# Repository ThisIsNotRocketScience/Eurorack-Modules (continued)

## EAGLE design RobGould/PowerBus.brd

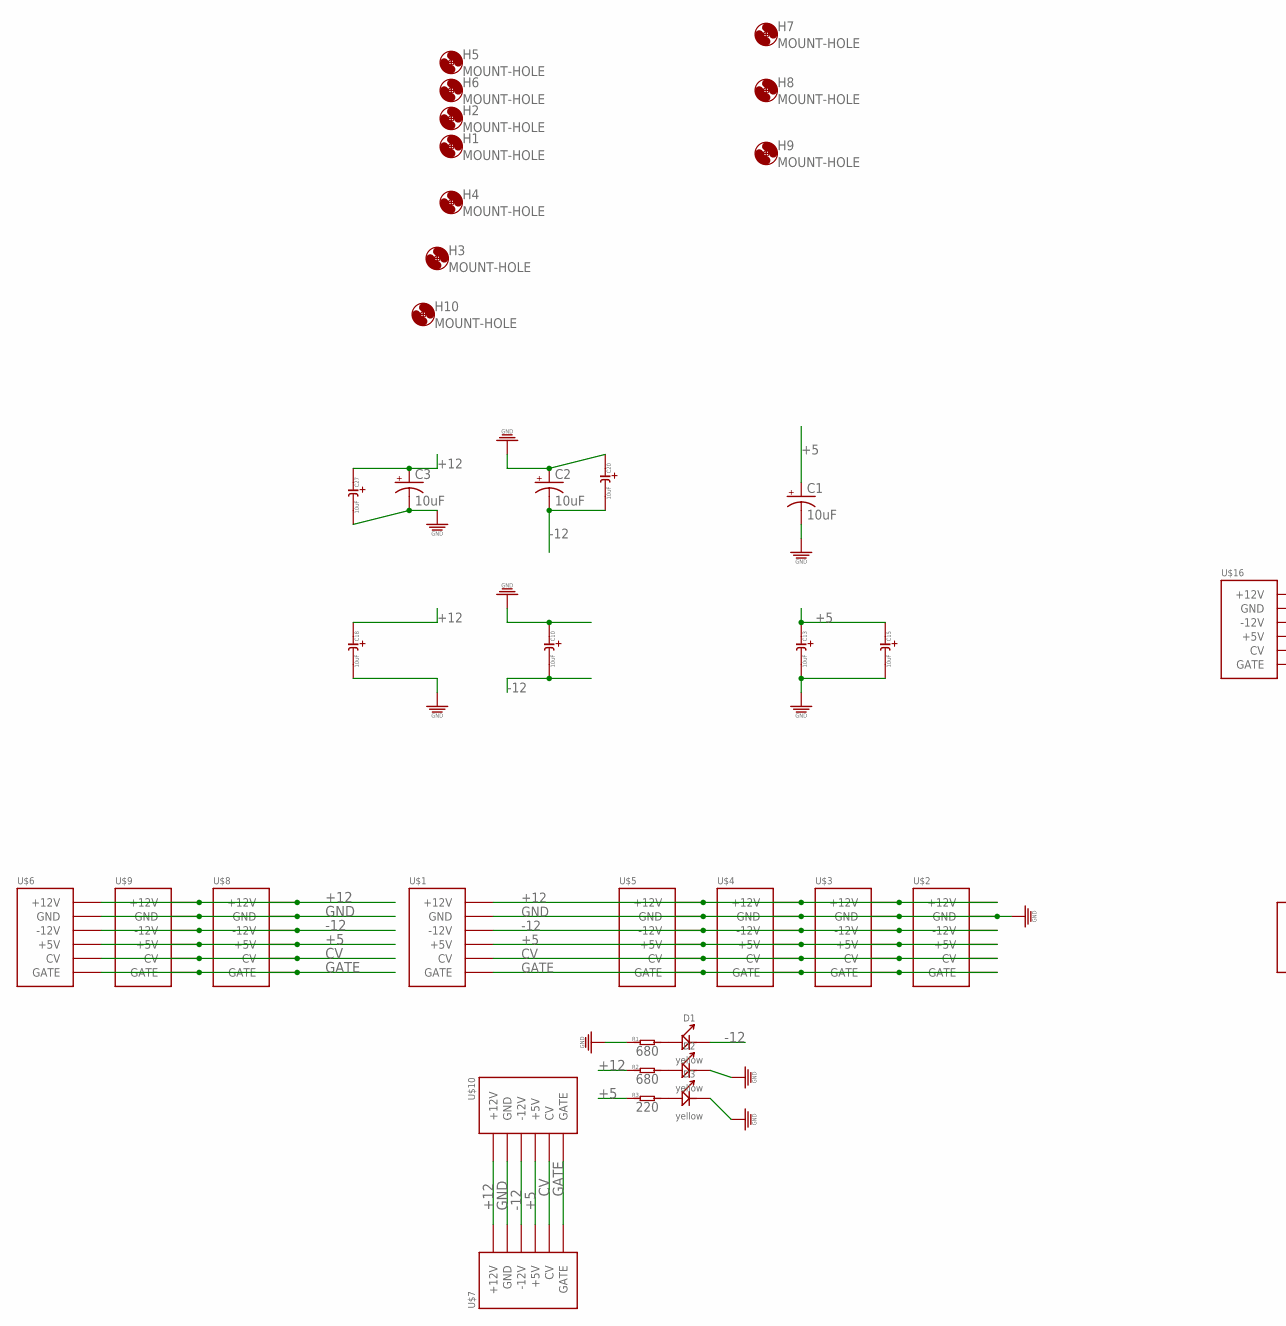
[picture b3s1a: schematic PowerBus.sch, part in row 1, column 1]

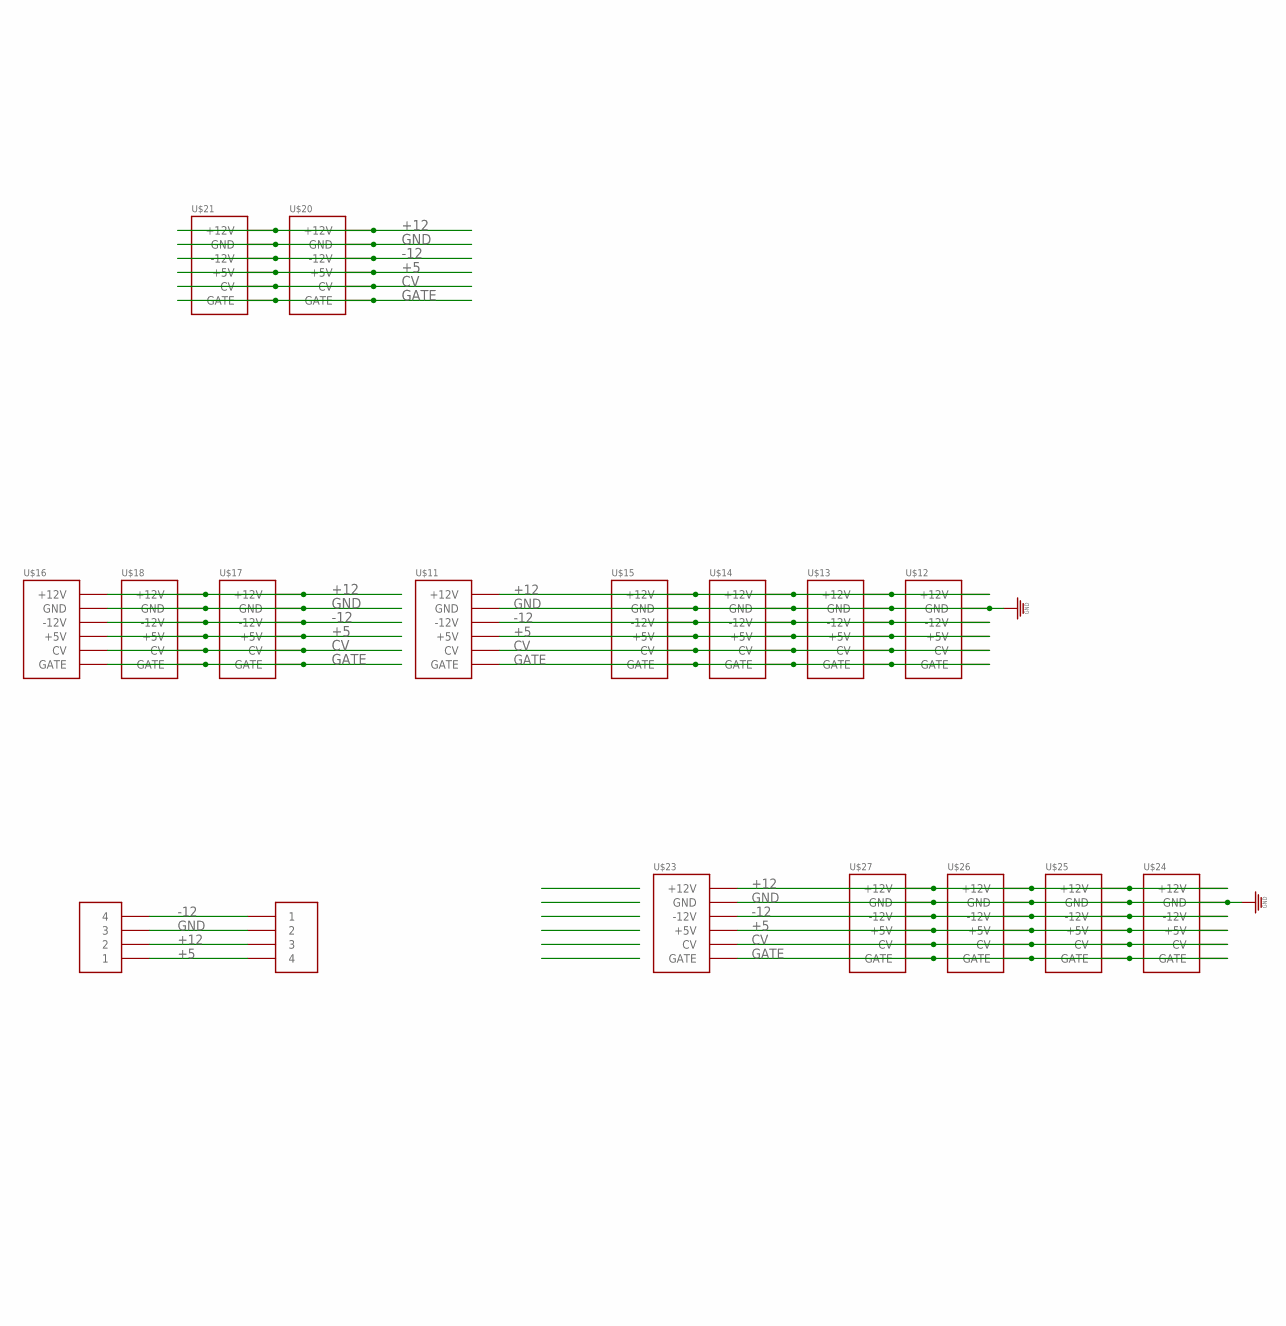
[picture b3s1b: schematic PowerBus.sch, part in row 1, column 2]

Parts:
C1, C2, C3: 10uF; PANASONIC_D
C10, C13, C15, C18, C20, C27: 10uF; CASE-A_3216
D1, D2, D3: yellow; LED0603
H1, H2, H3, H4, H5, H6, H7, H8, H9, H10: MOUNT-HOLE; 3.2-NOMARKINGS-SMALLSAFEZONE
R1, R2: 680; R0603
R3: 220; R0603
U$1, U$2, U$3, U$4, U$5, U$6, U$7, U$8, U$9, U$10, U$11, U$12, U$13, U$14, U$15, U$16, U$17, U$18, U$20, U$21, U$23, U$24, U$25, U$26, U$27: POWER_SHROUDED_NOTEXT; POWER_16_SHROUDED_NOTEXT
U$19, U$22: 4PIN5MM

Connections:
+5: C1.+, C13.+ (1), C15.+ (1), R3.1, U$1.11 (+5V), U$1.12 (+5V), U$2.11 (+5V), U$2.12 (+5V), U$3.11 (+5V), U$3.12 (+5V), U$4.11 (+5V), U$4.12 (+5V), U$5.11 (+5V), U$5.12 (+5V), U$6.11 (+5V), U$6.12 (+5V), U$7.11 (+5V), U$7.12 (+5V), U$8.11 (+5V), U$8.12 (+5V), U$9.11 (+5V), U$9.12 (+5V), U$10.11 (+5V), U$10.12 (+5V), U$11.11 (+5V), U$11.12 (+5V), U$12.11 (+5V), U$12.12 (+5V), U$13.11 (+5V), U$13.12 (+5V), U$14.11 (+5V), U$14.12 (+5V), U$15.11 (+5V), U$15.12 (+5V), U$16.11 (+5V), U$16.12 (+5V), U$17.11 (+5V), U$17.12 (+5V), U$18.11 (+5V), U$18.12 (+5V), U$19.4, U$20.11 (+5V), U$20.12 (+5V), U$21.11 (+5V), U$21.12 (+5V), U$22.1, U$23.11 (+5V), U$23.12 (+5V), U$24.11 (+5V), U$24.12 (+5V), U$25.11 (+5V), U$25.12 (+5V), U$26.11 (+5V), U$26.12 (+5V), U$27.11 (+5V), U$27.12 (+5V)
+12: C3.+, C18.+ (1), C27.+ (1), R2.1, U$1.9 (+12V), U$1.10 (+12V), U$2.9 (+12V), U$2.10 (+12V), U$3.9 (+12V), U$3.10 (+12V), U$4.9 (+12V), U$4.10 (+12V), U$5.9 (+12V), U$5.10 (+12V), U$6.9 (+12V), U$6.10 (+12V), U$7.9 (+12V), U$7.10 (+12V), U$8.9 (+12V), U$8.10 (+12V), U$9.9 (+12V), U$9.10 (+12V), U$10.9 (+12V), U$10.10 (+12V), U$11.9 (+12V), U$11.10 (+12V), U$12.9 (+12V), U$12.10 (+12V), U$13.9 (+12V), U$13.10 (+12V), U$14.9 (+12V), U$14.10 (+12V), U$15.9 (+12V), U$15.10 (+12V), U$16.9 (+12V), U$16.10 (+12V), U$17.9 (+12V), U$17.10 (+12V), U$18.9 (+12V), U$18.10 (+12V), U$19.3, U$20.9 (+12V), U$20.10 (+12V), U$21.9 (+12V), U$21.10 (+12V), U$22.2, U$23.9 (+12V), U$23.10 (+12V), U$24.9 (+12V), U$24.10 (+12V), U$25.9 (+12V), U$25.10 (+12V), U$26.9 (+12V), U$26.10 (+12V), U$27.9 (+12V), U$27.10 (+12V)
-12: C2.-, C10.- (2), C20.- (2), D1.-, U$1.1 (-12V), U$1.2 (-12V), U$2.1 (-12V), U$2.2 (-12V), U$3.1 (-12V), U$3.2 (-12V), U$4.1 (-12V), U$4.2 (-12V), U$5.1 (-12V), U$5.2 (-12V), U$6.1 (-12V), U$6.2 (-12V), U$7.1 (-12V), U$7.2 (-12V), U$8.1 (-12V), U$8.2 (-12V), U$9.1 (-12V), U$9.2 (-12V), U$10.1 (-12V), U$10.2 (-12V), U$11.1 (-12V), U$11.2 (-12V), U$12.1 (-12V), U$12.2 (-12V), U$13.1 (-12V), U$13.2 (-12V), U$14.1 (-12V), U$14.2 (-12V), U$15.1 (-12V), U$15.2 (-12V), U$16.1 (-12V), U$16.2 (-12V), U$17.1 (-12V), U$17.2 (-12V), U$18.1 (-12V), U$18.2 (-12V), U$19.1, U$20.1 (-12V), U$20.2 (-12V), U$21.1 (-12V), U$21.2 (-12V), U$22.4, U$23.1 (-12V), U$23.2 (-12V), U$24.1 (-12V), U$24.2 (-12V), U$25.1 (-12V), U$25.2 (-12V), U$26.1 (-12V), U$26.2 (-12V), U$27.1 (-12V), U$27.2 (-12V)
CV: U$1.13 (CV), U$1.14 (CV), U$2.13 (CV), U$2.14 (CV), U$3.13 (CV), U$3.14 (CV), U$4.13 (CV), U$4.14 (CV), U$5.13 (CV), U$5.14 (CV), U$6.13 (CV), U$6.14 (CV), U$7.13 (CV), U$7.14 (CV), U$8.13 (CV), U$8.14 (CV), U$9.13 (CV), U$9.14 (CV), U$10.13 (CV), U$10.14 (CV), U$11.13 (CV), U$11.14 (CV), U$12.13 (CV), U$12.14 (CV), U$13.13 (CV), U$13.14 (CV), U$14.13 (CV), U$14.14 (CV), U$15.13 (CV), U$15.14 (CV), U$16.13 (CV), U$16.14 (CV), U$17.13 (CV), U$17.14 (CV), U$18.13 (CV), U$18.14 (CV), U$20.13 (CV), U$20.14 (CV), U$21.13 (CV), U$21.14 (CV), U$23.13 (CV), U$23.14 (CV), U$24.13 (CV), U$24.14 (CV), U$25.13 (CV), U$25.14 (CV), U$26.13 (CV), U$26.14 (CV), U$27.13 (CV), U$27.14 (CV)
GATE: U$1.15 (GATE), U$1.16 (GATE), U$2.15 (GATE), U$2.16 (GATE), U$3.15 (GATE), U$3.16 (GATE), U$4.15 (GATE), U$4.16 (GATE), U$5.15 (GATE), U$5.16 (GATE), U$6.15 (GATE), U$6.16 (GATE), U$7.15 (GATE), U$7.16 (GATE), U$8.15 (GATE), U$8.16 (GATE), U$9.15 (GATE), U$9.16 (GATE), U$10.15 (GATE), U$10.16 (GATE), U$11.15 (GATE), U$11.16 (GATE), U$12.15 (GATE), U$12.16 (GATE), U$13.15 (GATE), U$13.16 (GATE), U$14.15 (GATE), U$14.16 (GATE), U$15.15 (GATE), U$15.16 (GATE), U$16.15 (GATE), U$16.16 (GATE), U$17.15 (GATE), U$17.16 (GATE), U$18.15 (GATE), U$18.16 (GATE), U$20.15 (GATE), U$20.16 (GATE), U$21.15 (GATE), U$21.16 (GATE), U$23.15 (GATE), U$23.16 (GATE), U$24.15 (GATE), U$24.16 (GATE), U$25.15 (GATE), U$25.16 (GATE), U$26.15 (GATE), U$26.16 (GATE), U$27.15 (GATE), U$27.16 (GATE)
GND: C1.-, C2.+, C3.-, C10.+ (1), C13.- (2), C15.- (2), C18.- (2), C20.+ (1), C27.- (2), D2.-, D3.-, R1.1, U$1.3 (GND), U$1.4 (GND), U$1.5 (GND), U$1.6 (GND), U$1.7 (GND), U$1.8 (GND), U$2.3 (GND), U$2.4 (GND), U$2.5 (GND), U$2.6 (GND), U$2.7 (GND), U$2.8 (GND), U$3.3 (GND), U$3.4 (GND), U$3.5 (GND), U$3.6 (GND), U$3.7 (GND), U$3.8 (GND), U$4.3 (GND), U$4.4 (GND), U$4.5 (GND), U$4.6 (GND), U$4.7 (GND), U$4.8 (GND), U$5.3 (GND), U$5.4 (GND), U$5.5 (GND), U$5.6 (GND), U$5.7 (GND), U$5.8 (GND), U$6.3 (GND), U$6.4 (GND), U$6.5 (GND), U$6.6 (GND), U$6.7 (GND), U$6.8 (GND), U$7.3 (GND), U$7.4 (GND), U$7.5 (GND), U$7.6 (GND), U$7.7 (GND), U$7.8 (GND), U$8.3 (GND), U$8.4 (GND), U$8.5 (GND), U$8.6 (GND), U$8.7 (GND), U$8.8 (GND), U$9.3 (GND), U$9.4 (GND), U$9.5 (GND), U$9.6 (GND), U$9.7 (GND), U$9.8 (GND), U$10.3 (GND), U$10.4 (GND), U$10.5 (GND), U$10.6 (GND), U$10.7 (GND), U$10.8 (GND), U$11.3 (GND), U$11.4 (GND), U$11.5 (GND), U$11.6 (GND), U$11.7 (GND), U$11.8 (GND), U$12.3 (GND), U$12.4 (GND), U$12.5 (GND), U$12.6 (GND), U$12.7 (GND), U$12.8 (GND), U$13.3 (GND), U$13.4 (GND), U$13.5 (GND), U$13.6 (GND), U$13.7 (GND), U$13.8 (GND), U$14.3 (GND), U$14.4 (GND), U$14.5 (GND), U$14.6 (GND), U$14.7 (GND), U$14.8 (GND), U$15.3 (GND), U$15.4 (GND), U$15.5 (GND), U$15.6 (GND), U$15.7 (GND), U$15.8 (GND), U$16.3 (GND), U$16.4 (GND), U$16.5 (GND), U$16.6 (GND), U$16.7 (GND), U$16.8 (GND), U$17.3 (GND), U$17.4 (GND), U$17.5 (GND), U$17.6 (GND), U$17.7 (GND), U$17.8 (GND), U$18.3 (GND), U$18.4 (GND), U$18.5 (GND), U$18.6 (GND), U$18.7 (GND), U$18.8 (GND), U$19.2, U$20.3 (GND), U$20.4 (GND), U$20.5 (GND), U$20.6 (GND), U$20.7 (GND), U$20.8 (GND), U$21.3 (GND), U$21.4 (GND), U$21.5 (GND), U$21.6 (GND), U$21.7 (GND), U$21.8 (GND), U$22.3, U$23.3 (GND), U$23.4 (GND), U$23.5 (GND), U$23.6 (GND), U$23.7 (GND), U$23.8 (GND), U$24.3 (GND), U$24.4 (GND), U$24.5 (GND), U$24.6 (GND), U$24.7 (GND), U$24.8 (GND), U$25.3 (GND), U$25.4 (GND), U$25.5 (GND), U$25.6 (GND), U$25.7 (GND), U$25.8 (GND), U$26.3 (GND), U$26.4 (GND), U$26.5 (GND), U$26.6 (GND), U$26.7 (GND), U$26.8 (GND), U$27.3 (GND), U$27.4 (GND), U$27.5 (GND), U$27.6 (GND), U$27.7 (GND), U$27.8 (GND)
unnamed: D1.+, R1.2
unnamed: D2.+, R2.2
unnamed: D3.+, R3.2

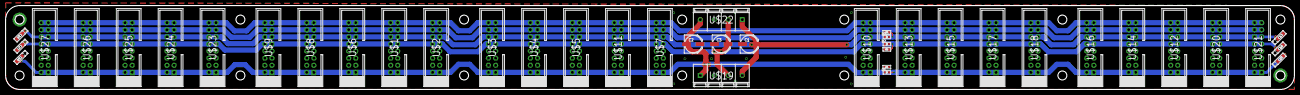
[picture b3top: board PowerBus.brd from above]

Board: 2 copper layers, 461.0 x 30.0 mm, 54 parts (0 on the bottom side), 9 nets.

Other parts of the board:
H11, H12: MOUNT-HOLE; 3.2-NOMARKINGS-SMALLSAFEZONE

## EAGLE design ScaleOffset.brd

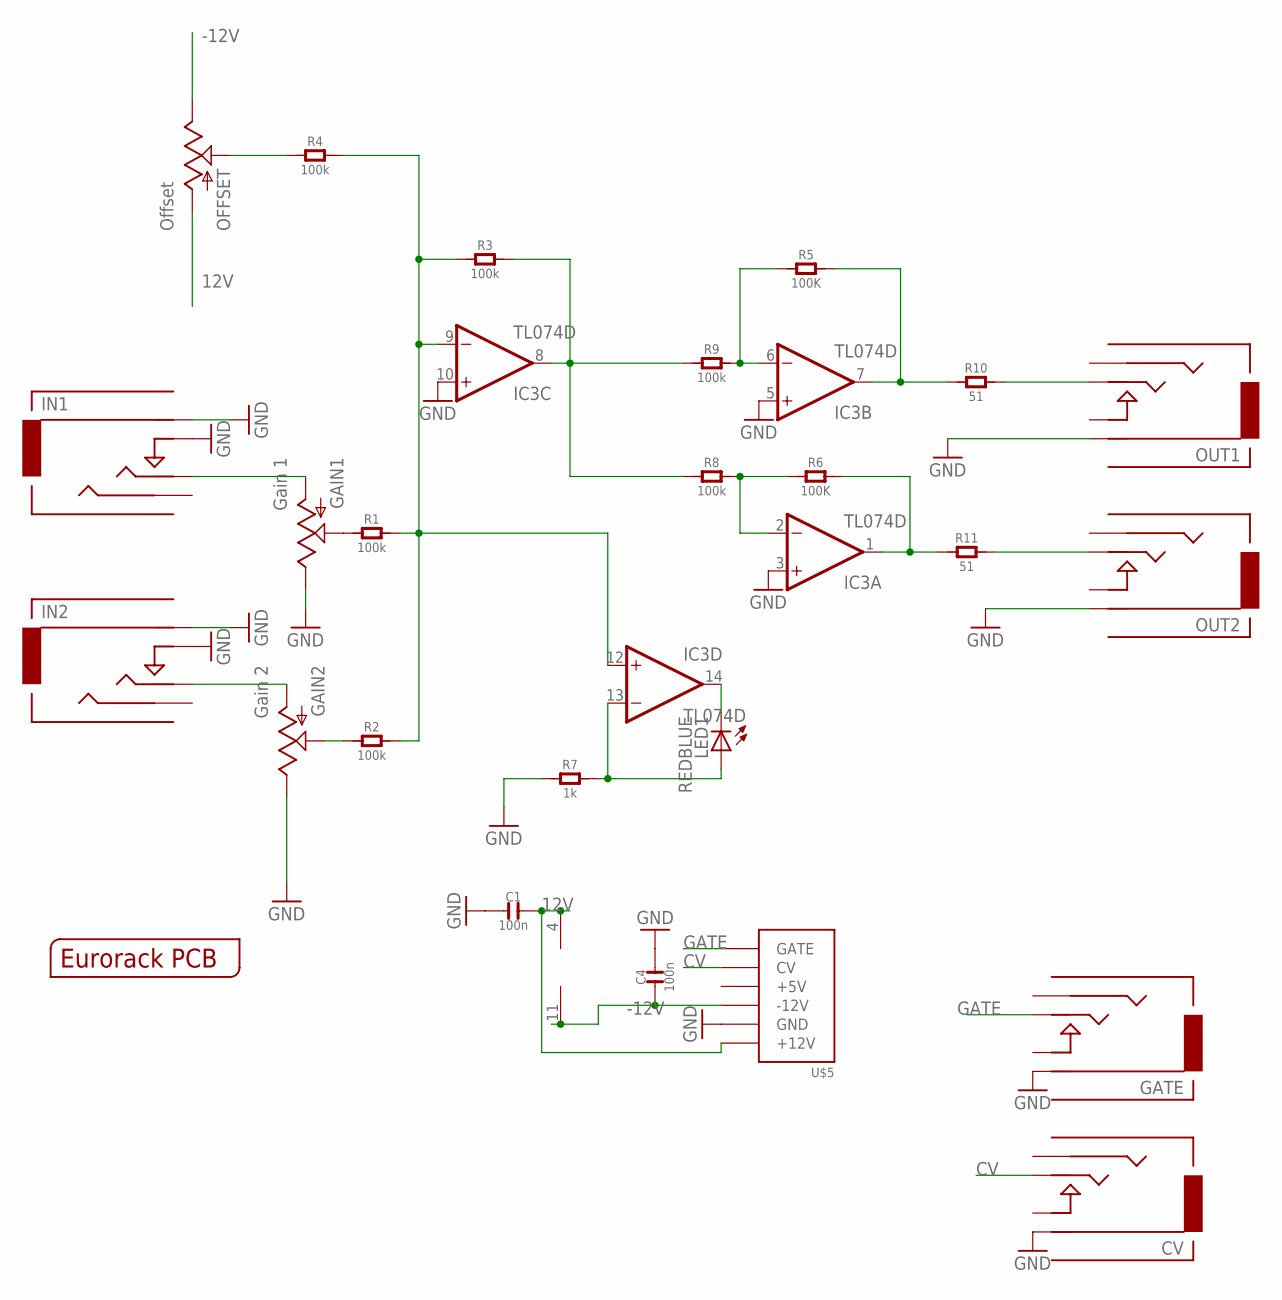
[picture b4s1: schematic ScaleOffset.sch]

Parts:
C1, C4: 100n; C0603
CV: CV; 3.5MM-JACK-SWITCH-13MM-OUTPUT
GAIN1: Gain 1; OG-POTS_ALPS_POT_VERTICAL
GAIN2: Gain 2; OG-POTS_ALPS_POT_VERTICAL
GATE: GATE; 3.5MM-JACK-SWITCH-13MM-OUTPUT
IC3: TL074D; SO14
IN1: Input 1; 3.5MM-JACK-SWITCH-13MM-INPUT
IN2: Input 2; 3.5MM-JACK-SWITCH-13MM-INPUT
LED1: REDBLUE; LED3MM
OFFSET: Offset; OG-POTS_ALPS_POT_VERTICAL
OUT1: 2; 3.5MM-JACK-SWITCH-13MM-OUTPUT
OUT2: 1; 3.5MM-JACK-SWITCH-13MM-OUTPUT
R1, R2, R3, R4, R8, R9: 100k; R0603
R5, R6: 100K; R0603
R7: 1k; R0603
R10, R11: 51; R0603
U$5: POWER; POWER_16
U$12: EURORACK_PCB6HP; EURORACK6HPPCB

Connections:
12V: C1.2, IC3.4 (V+), OFFSET.P$3 (A), U$5.9 (+12V), U$5.10 (+12V)
-12V: C4.1, IC3.11 (V-), OFFSET.P$1 (E), U$5.1 (-12V), U$5.2 (-12V)
CV: CV.TIP@1 (TIP), CV.TIP@2 (TIP), U$5.13 (CV), U$5.14 (CV)
FBOUT1: IC3.7 (OUT), R5.2, R10.1
FBOUT2: IC3.1 (OUT), R6.2, R11.1
GATE: GATE.TIP@1 (TIP), GATE.TIP@2 (TIP), U$5.15 (GATE), U$5.16 (GATE)
GND: C1.1, C4.2, CV.RING@1 (RING), CV.RING@2 (RING), GAIN1.P$1 (E), GAIN2.P$1 (E), GATE.RING@1 (RING), GATE.RING@2 (RING), IC3.3 (+IN), IC3.5 (+IN), IC3.10 (+IN), IN1.RING@1 (RING), IN1.RING@2 (RING), IN1.SWITCH@1 (SWITCH), IN1.SWITCH@2 (SWITCH), IN2.RING@1 (RING), IN2.RING@2 (RING), IN2.SWITCH@1 (SWITCH), IN2.SWITCH@2 (SWITCH), OUT1.RING@1 (RING), OUT1.RING@2 (RING), OUT2.RING@1 (RING), OUT2.RING@2 (RING), R7.1, U$5.3 (GND), U$5.4 (GND), U$5.5 (GND), U$5.6 (GND), U$5.7 (GND), U$5.8 (GND)
unnamed: IC3.6 (-IN), R5.1, R9.2
unnamed: GAIN2.P$3 (A), IN2.TIP@1 (TIP), IN2.TIP@2 (TIP)
unnamed: GAIN1.P$3 (A), IN1.TIP@1 (TIP), IN1.TIP@2 (TIP)
unnamed: GAIN1.P$2 (S), R1.1
unnamed: GAIN2.P$2 (S), R2.1
unnamed: IC3.8 (OUT), R3.2, R8.1, R9.1
unnamed: IC3.14 (OUT), LED1.K (C)
unnamed: IC3.13 (-IN), LED1.A, R7.2
unnamed: IC3.2 (-IN), R6.1, R8.2
OFFSET: OFFSET.P$2 (S), R4.1
OUT1: OUT1.TIP@1 (TIP), OUT1.TIP@2 (TIP), R10.2
OUT2: OUT2.TIP@1 (TIP), OUT2.TIP@2 (TIP), R11.2
SUMMING: IC3.9 (-IN), IC3.12 (+IN), R1.2, R2.2, R3.1, R4.2

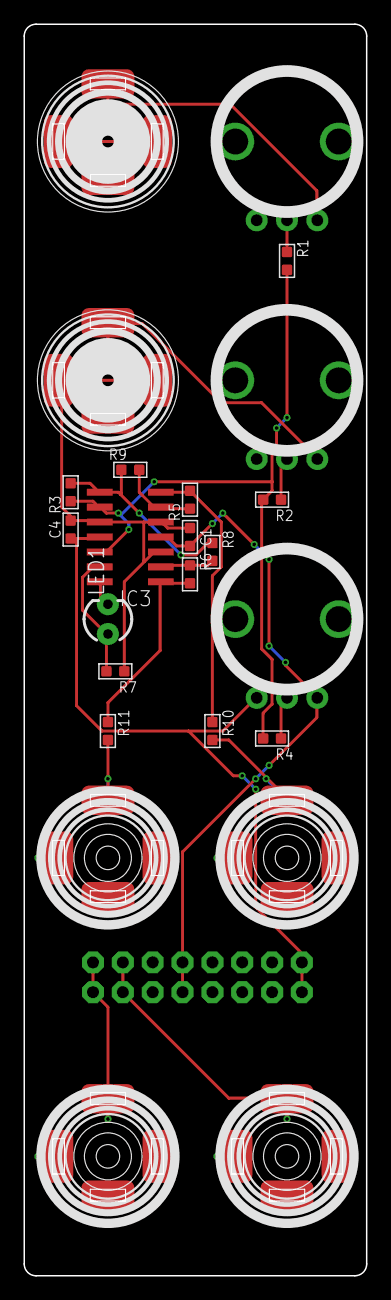
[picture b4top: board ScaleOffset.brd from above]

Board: 2 copper layers, 29.1 x 106.5 mm, 26 parts (1 on the bottom side), 20 nets.

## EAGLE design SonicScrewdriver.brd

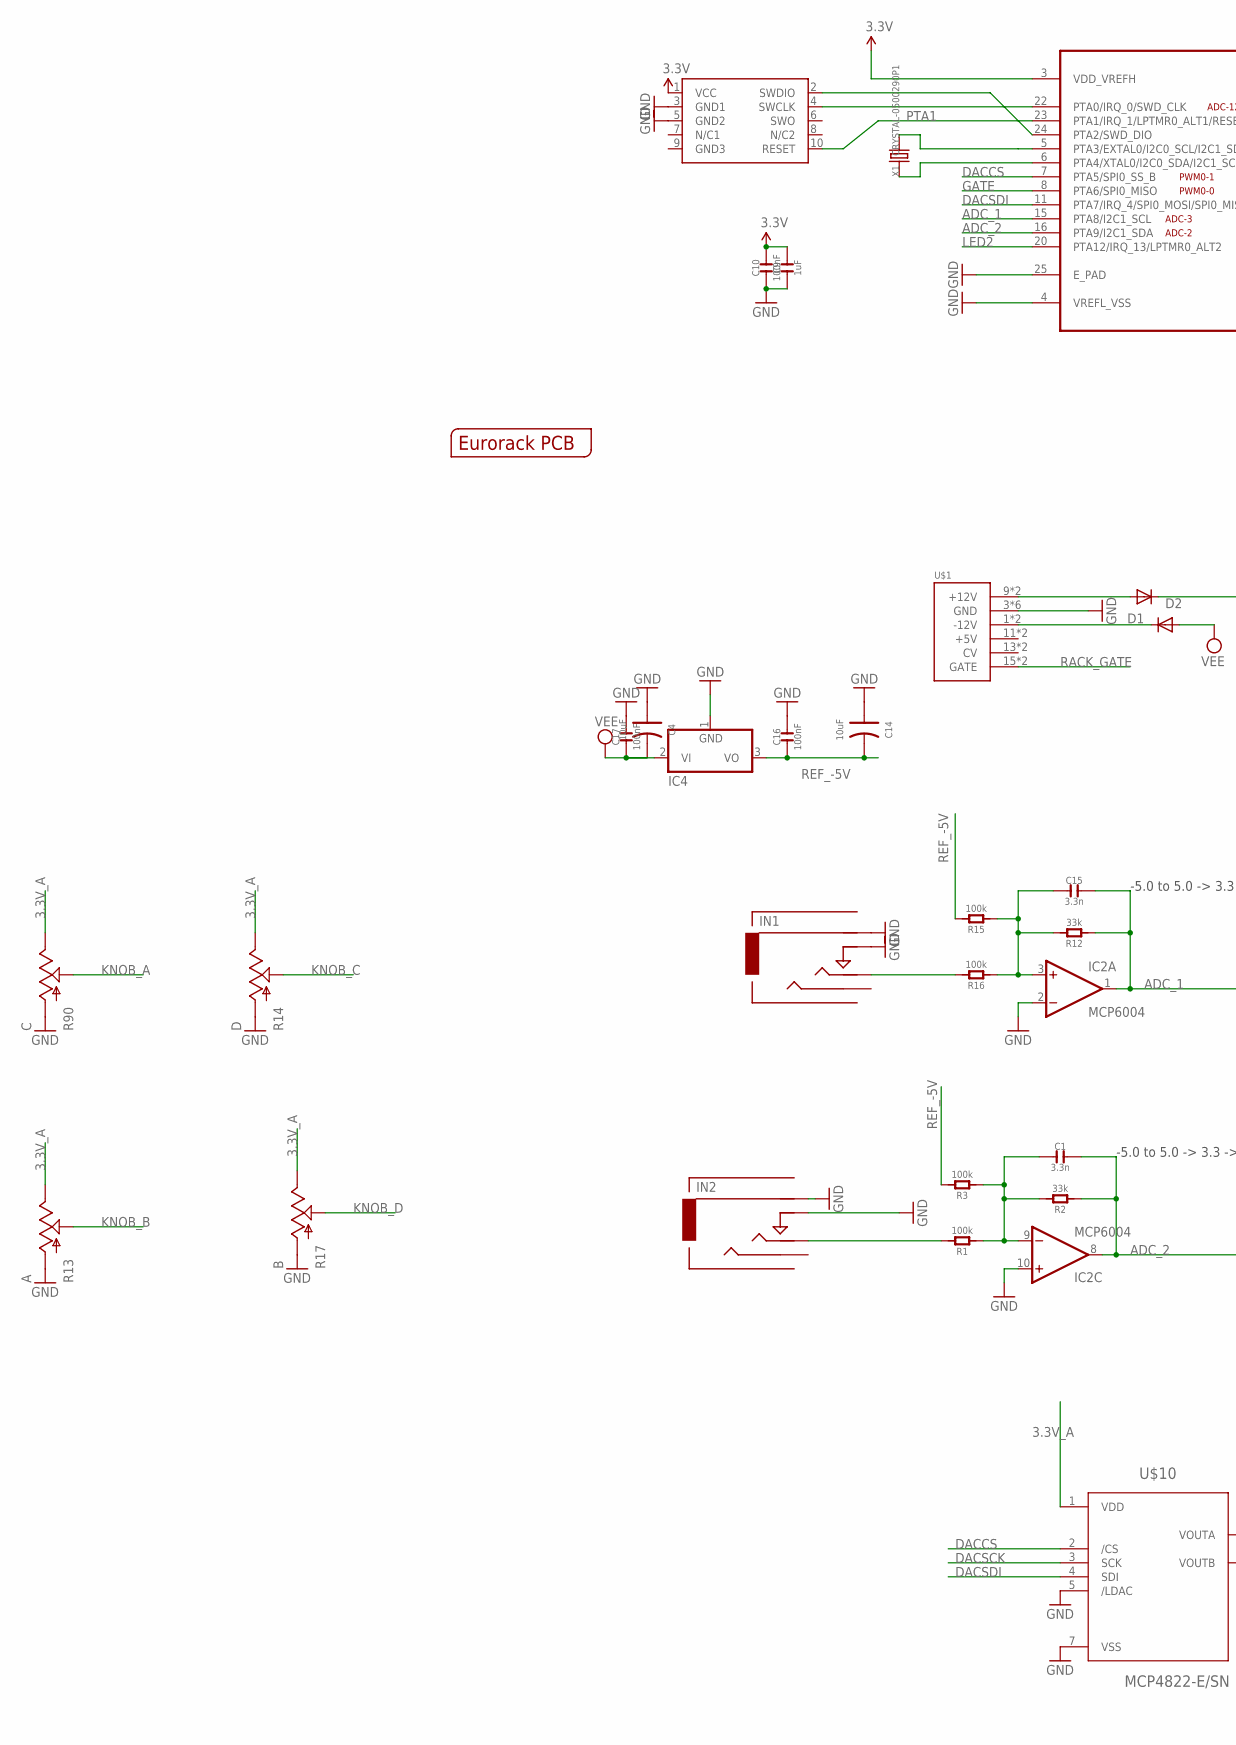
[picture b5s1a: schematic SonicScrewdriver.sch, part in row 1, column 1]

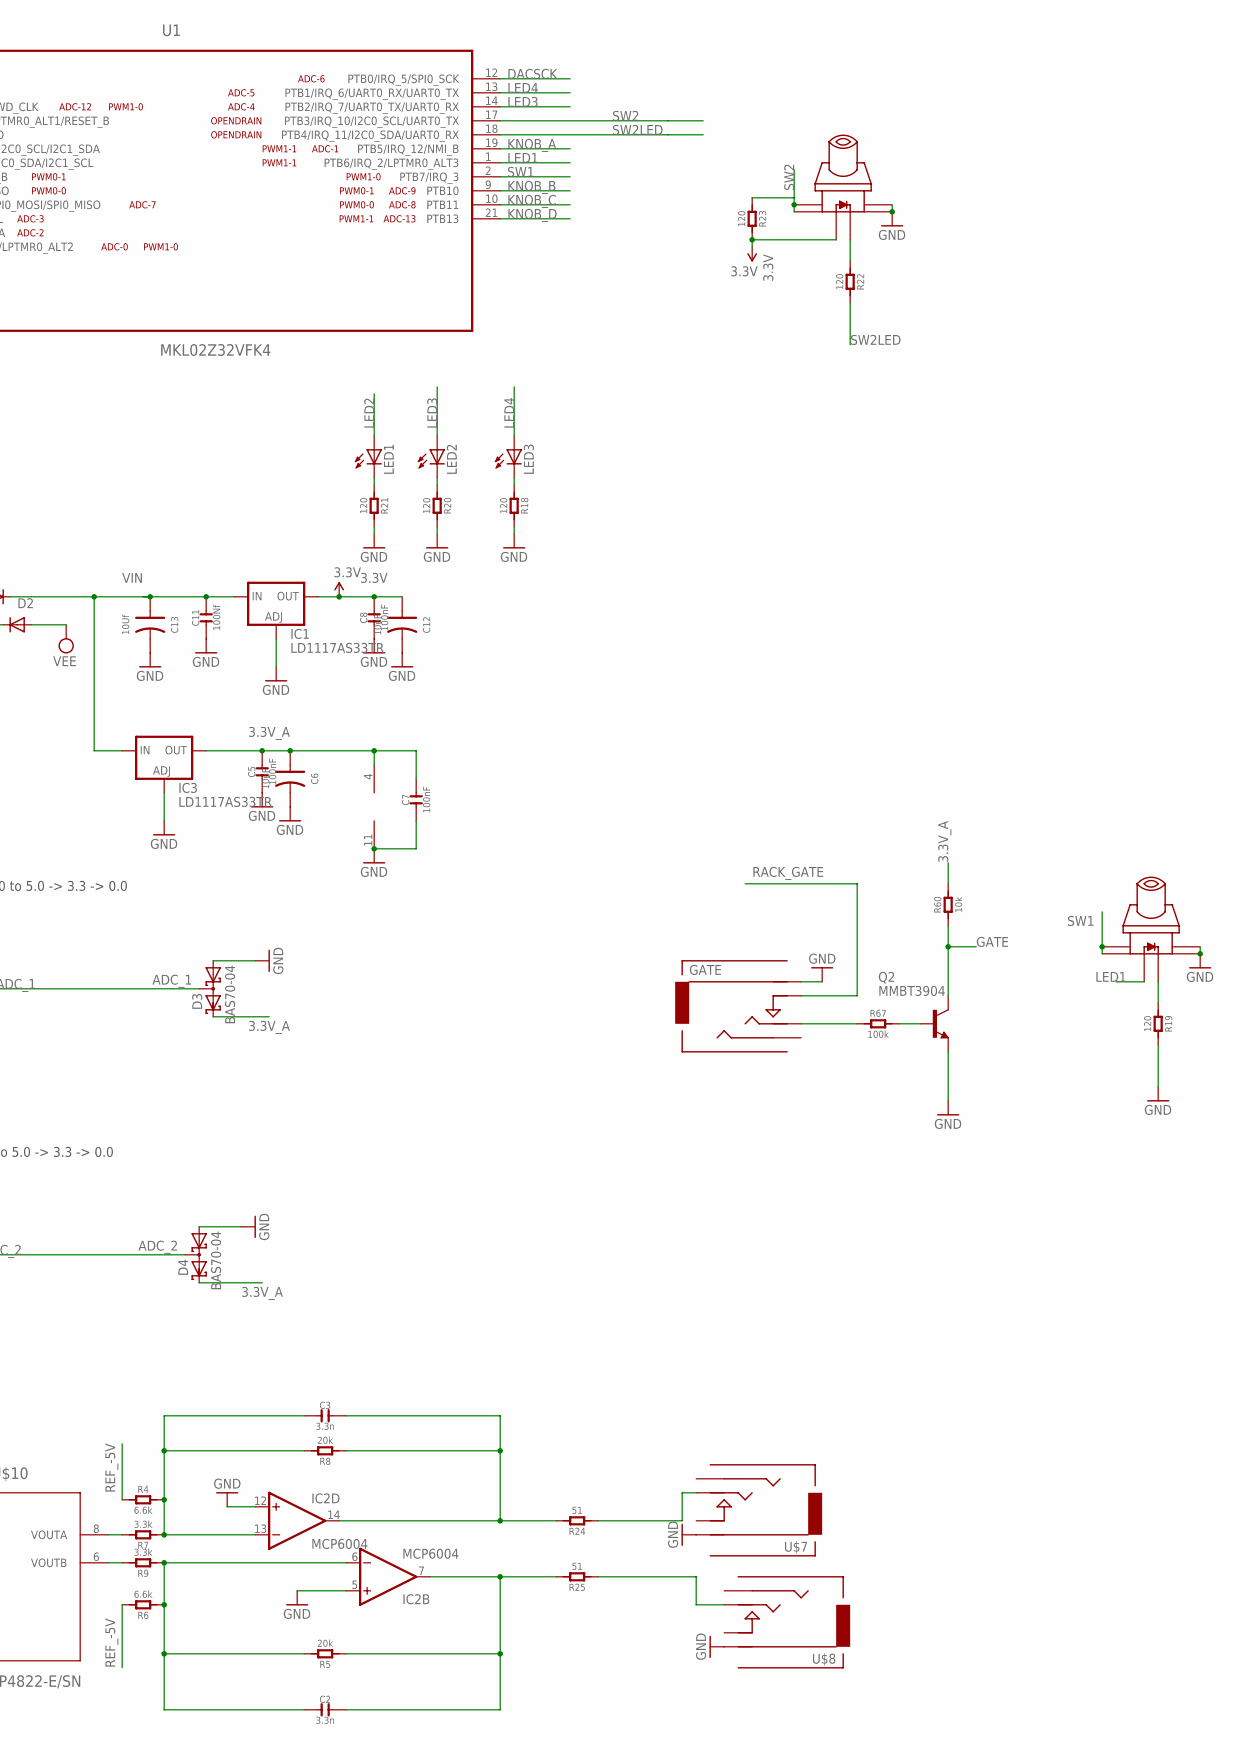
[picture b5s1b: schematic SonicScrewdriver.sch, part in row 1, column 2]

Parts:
C1, C2, C3, C15: 3.3n; C0603
C4, C6, C12, C14: 10uF; AVX-A
C5, C7, C8, C10, C16, C17: 100nF; C0603
C9: 1uF; C0603
C11: 100Nf; C0603
C13: 10Uf; AVX-A
D1, D2: 1N5819HW; SOD123
D3, D4: BAS70-04; SOT23
GATE: Gate; 3.5MM-JACK-SWITCH-13MM-INPUT
IC1, IC3: LD1117AS33TR; SOT223
IC2: MCP6004; SO14
IC4: 7905T; TO220H
IN1: In 2; 3.5MM-JACK-SWITCH-13MM-INPUT
IN2: In 1; 3.5MM-JACK-SWITCH-13MM-INPUT
LED1, LED2, LED3: LED3MM
Q2: MMBT3904; SOT23-BEC
R1, R3, R15, R16, R67: 100k; R0603
R2, R12: 33k; R0603
R4, R6: 6.6k; R0603
R5, R8: 20k; R0603
R7, R9: 3.3k; R0603
R13: A; OG-POTS_ALPS_POT_VERTICAL
R14: D; OG-POTS_ALPS_POT_VERTICAL
R17: B; OG-POTS_ALPS_POT_VERTICAL
R18, R19, R20, R21, R22, R23: 120; R0603
R24, R25: 51; R0603
R60: 10k; R0603
R90: C; OG-POTS_ALPS_POT_VERTICAL
SWD1: CORTEX_SWD; M50-3600542
U1: MKL02Z32VFK4; QFN50P400X400X100-25N
U$1: POWER; POWER_16
U$2: EURORACK_PCB8HP; EURORACK8HPPCB
U$3, U$6: SWITCH_W_LED_PB6149L-X-102WHITE; PB6149L
U$7: Out 2; 3.5MM-JACK-SWITCH-13MM-OUTPUT
U$8: Out 1; 3.5MM-JACK-SWITCH-13MM-OUTPUT
U$10: MCP4822-E/SN; SOIC8-N_MC
X1: CRYSTAL-0500290P1; 2P-SMD-5.0X3.2

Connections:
3.3V: C8.2, C9.2, C10.2, C12.+ (1), IC1.2 (OUT), IC1.4 (OUT), R23.2, SWD1.1 (VCC), U1.3 (VDD_VREFH), U$3.LEDPOS (POS)
3.3V_A: C5.2, C6.+ (1), C7.2, D3.2 (C2), D4.2 (C2), IC2.4 (V+), IC3.2 (OUT), IC3.4 (OUT), R13.P$1 (E), R14.P$1 (E), R17.P$1 (E), R60.2, R90.P$1 (E), U$10.1 (VDD)
ADC_1: C15.2, D3.3 (C1A2), IC2.1 (OUT), R12.1, U1.15 (PTA8/I2C1_SCL)
ADC_2: C1.2, D4.3 (C1A2), IC2.8 (OUT), R2.1, U1.16 (PTA9/I2C1_SDA)
DACCS: U1.7 (PTA5/SPI0_SS_B), U$10.2 (/CS)
DACSCK: U1.12 (PTB0/IRQ_5/SPI0_SCK), U$10.3 (SCK)
DACSDI: U1.11 (PTA7/IRQ_4/SPI0_MOSI/SPI0_MISO), U$10.4 (SDI)
GATE: Q2.C, R60.1, U1.8 (PTA6/SPI0_MISO)
GND: C4.+ (1), C5.1, C6.- (2), C7.1, C8.1, C9.1, C10.1, C11.1, C12.- (2), C13.- (2), C14.+ (1), C16.2, C17.2, D3.1 (A1), D4.1 (A1), GATE.RING@1 (RING), GATE.RING@2 (RING), IC1.1 (ADJ), IC2.2 (-IN), IC2.5 (+IN), IC2.10 (+IN), IC2.11 (V-), IC2.12 (+IN), IC3.1 (ADJ), IC4.1 (GND), IN1.RING@1 (RING), IN1.RING@2 (RING), IN1.SWITCH@1 (SWITCH), IN1.SWITCH@2 (SWITCH), IN2.RING@1 (RING), IN2.RING@2 (RING), IN2.SWITCH@1 (SWITCH), IN2.SWITCH@2 (SWITCH), Q2.E, R13.P$3 (A), R14.P$3 (A), R17.P$3 (A), R18.2, R19.2, R20.2, R21.2, R90.P$3 (A), SWD1.3 (GND1), SWD1.5 (GND2), U1.4 (VREFL_VSS), U1.25 (E_PAD), U$1.3 (GND), U$1.4 (GND), U$1.5 (GND), U$1.6 (GND), U$1.7 (GND), U$1.8 (GND), U$3.3, U$3.4, U$6.3, U$6.4, U$7.RING@1 (RING), U$7.RING@2 (RING), U$8.RING@1 (RING), U$8.RING@2 (RING), U$10.5 (/LDAC), U$10.7 (VSS)
KNOB_A: R90.P$2 (S), U1.19 (PTB5/IRQ_12/NMI_B)
KNOB_B: R13.P$2 (S), U1.9 (PTB10)
KNOB_C: R14.P$2 (S), U1.10 (PTB11)
KNOB_D: R17.P$2 (S), U1.21 (PTB13)
LED1: U1.1 (PTB6/IRQ_2/LPTMR0_ALT3), U$6.LEDPOS (POS)
LED2: LED1.A, U1.20 (PTA12/IRQ_13/LPTMR0_ALT2)
LED3: LED2.A, U1.14 (PTB2/IRQ_7/UART0_TX/UART0_RX)
LED4: LED3.A, U1.13 (PTB1/IRQ_6/UART0_RX/UART0_TX)
unnamed: U1.5 (PTA3/EXTAL0/I2C0_SCL/I2C1_SDA), X1.2
unnamed: U1.6 (PTA4/XTAL0/I2C0_SDA/I2C1_SCL), X1.1
unnamed: IN1.TIP@1 (TIP), IN1.TIP@2 (TIP), R16.2
unnamed: C15.1, IC2.3 (+IN), R12.2, R15.1, R16.1
unnamed: SWD1.4 (SWCLK), U1.22 (PTA0/IRQ_0/SWD_CLK)
unnamed: IN2.TIP@1 (TIP), IN2.TIP@2 (TIP), R1.2
unnamed: SWD1.2 (SWDIO), U1.24 (PTA2/SWD_DIO)
unnamed: C1.1, IC2.9 (-IN), R1.1, R2.2, R3.1
unnamed: C2.1, IC2.6 (-IN), R5.2, R6.1, R9.1
unnamed: C3.1, IC2.13 (-IN), R4.2, R7.1, R8.2
unnamed: R7.2, U$10.8 (VOUTA)
unnamed: R9.2, U$10.6 (VOUTB)
unnamed: D1.A, U$1.9 (+12V), U$1.10 (+12V)
unnamed: R19.1, U$6.LEDNEG (NEG)
unnamed: LED3.K (C), R18.1
unnamed: LED2.K (C), R20.1
unnamed: LED1.K (C), R21.1
unnamed: C3.2, IC2.14 (OUT), R8.1, R24.2
unnamed: R22.1, U$3.LEDNEG (NEG)
unnamed: R25.1, U$8.TIP@1 (TIP), U$8.TIP@2 (TIP)
unnamed: R24.1, U$7.TIP@1 (TIP), U$7.TIP@2 (TIP)
unnamed: C2.2, IC2.7 (OUT), R5.1, R25.2
unnamed: GATE.TIP@1 (TIP), GATE.TIP@2 (TIP), R67.1
unnamed: D2.C, U$1.1 (-12V), U$1.2 (-12V)
unnamed: Q2.B, R67.2
PTA1: SWD1.10 (RESET), U1.23 (PTA1/IRQ_1/LPTMR0_ALT1/RESET_B)
RACK_GATE: GATE.SWITCH@1 (SWITCH), GATE.SWITCH@2 (SWITCH), U$1.15 (GATE), U$1.16 (GATE)
REF_-5V: C14.- (2), C16.1, IC4.3 (VO), R3.2, R4.1, R6.2, R15.2
SW1: U1.2 (PTB7/IRQ_3), U$6.1, U$6.2
SW2: R23.1, U1.17 (PTB3/IRQ_10/I2C0_SCL/UART0_TX), U$3.1, U$3.2
SW2LED: R22.2, U1.18 (PTB4/IRQ_11/I2C0_SDA/UART0_RX)
VEE: C4.- (2), C17.1, D2.A, IC4.2 (VI)
VIN: C11.2, C13.+ (1), D1.C, IC1.3 (IN), IC3.3 (IN)

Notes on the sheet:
-5.0 to 5.0 -> 3.3 -> 0.0

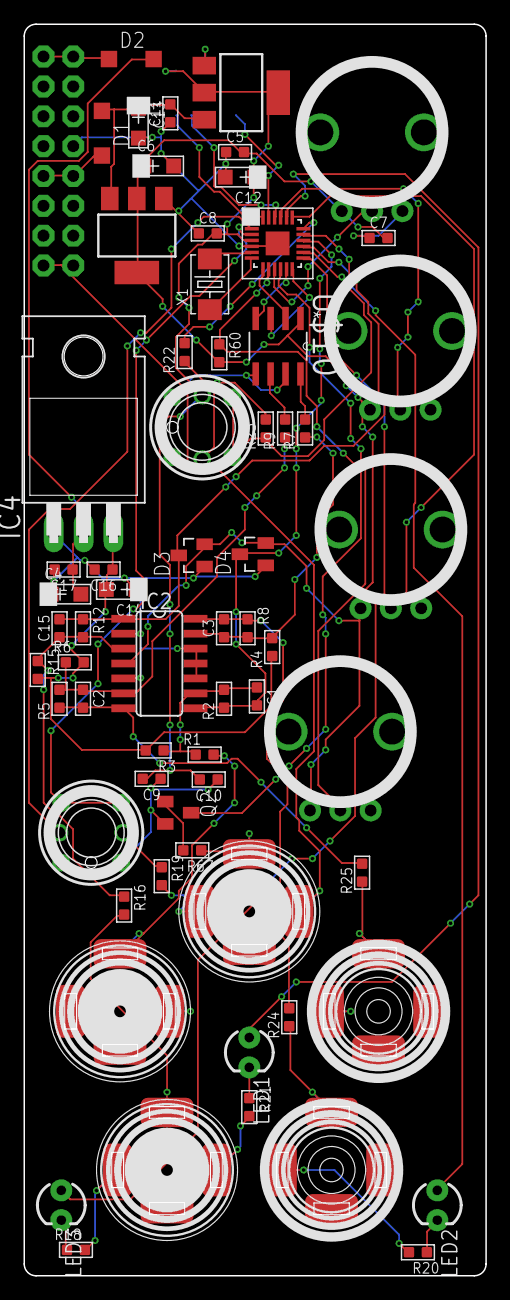
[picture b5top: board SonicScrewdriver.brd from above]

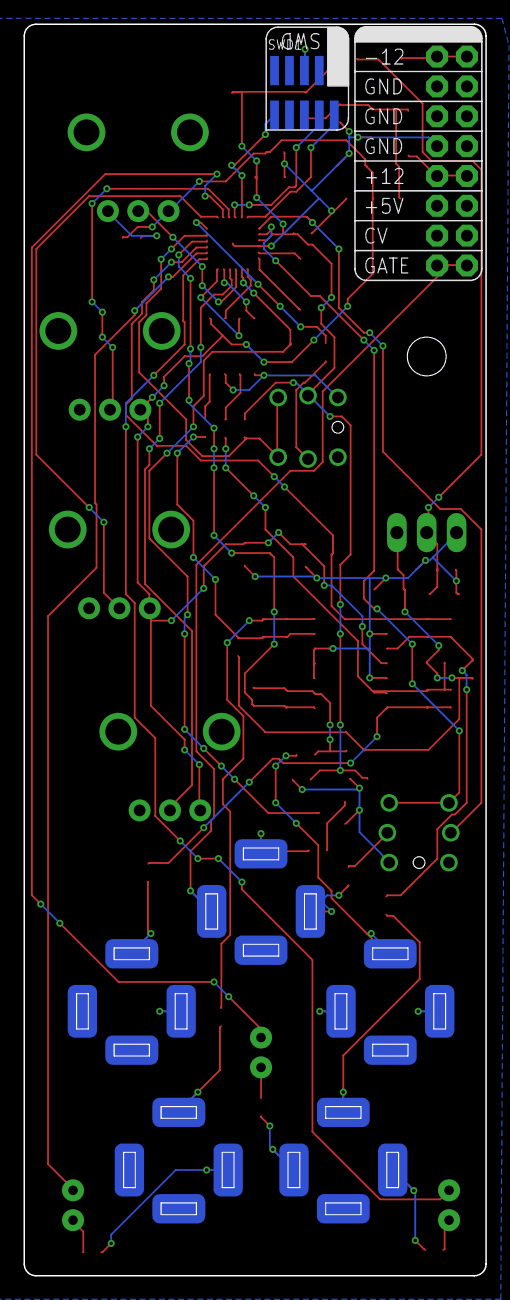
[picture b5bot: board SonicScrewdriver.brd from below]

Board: 2 copper layers, 39.3 x 106.5 mm, 68 parts (2 on the bottom side), 50 nets.
